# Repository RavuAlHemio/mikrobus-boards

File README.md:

# mikroBUS Boards

An assortment of boards that should be compatible with [MikroElektronika](https://www.mikroe.com/)'s [mikroBUS standard](https://download.mikroe.com/documents/standards/mikrobus/mikrobus-standard-specification-v200.pdf).

The designs are experimental. They are provided without warranty that the resulting boards will be fit for purpose and without warranty that they will not damage the connected devices.

## Boards

* `i2c-spi-jumper-mikrobus-board`: an I²C-to-SPI interface similar to the [_I2C to SPI Click_](https://www.mikroe.com/i2c-to-spi-click) (MIKROE-3743) and using the same chip ([NXP SC18IS602BIPW/S8HP](https://www.nxp.com/part/SC18IS602BIPW)), but with pin header jumpers instead of re-soldering 0Ω SMD "resistors" to set the I²C address. Perfect for people with no fine motor skills, like myself.

* `i2c-spi-jumper-mikrobus-board-var2`: another I²C-to-SPI interface with jumpers, but using the [NXP SC18IS606PW](https://www.nxp.com/part/SC18IS606PW), since the SC18IS602BIPW/S8HP is end-of-life. A different board is needed because the new chip has a different pinout.

* `i2c-spi-oled-mikrobus-board`: an I²C-to-SPI interface with a pinout that helps interoperability with the [_OLED C Click_] (https://www.mikroe.com/oled-c-click) (MIKROE-1585) by making some of its additional non-SPI pins accessible via I²C while isolating them from the microcontroller. To simplify the traces and keep the board a reasonable size, instead of providing a second pair of mikroBUS sockets to connect the SPI-enabled device, the design provides a [mikroBUS Shuttle](https://www.mikroe.com/mikrobus-shuttle) pin header.

* `i2c-uart-mikrobus-board`: just as the I²C-to-SPI boards allow SPI devices to be controlled via I²C, this board allows UART devices to be contacted via I²C. Based around the [NXP SC16IS740IPW](https://www.nxp.com/part/SC16IS740IPW). This board also provides a [mikroBUS Shuttle](https://www.mikroe.com/mikrobus-shuttle) pin header to connect the UART board. The I²C address is set using rotary switches.

* `knx-mikrobus-board`: a KNX bus coupling unit (BCU) that translates between KNX and UART. Based around the [onsemi NCN5130](https://www.onsemi.com/products/interfaces/wired-transceivers-modems/ncn5130) but should also work with the pin-compatible [onsemi NCN5121](https://www.onsemi.com/products/interfaces/wired-transceivers-modems/ncn5121).

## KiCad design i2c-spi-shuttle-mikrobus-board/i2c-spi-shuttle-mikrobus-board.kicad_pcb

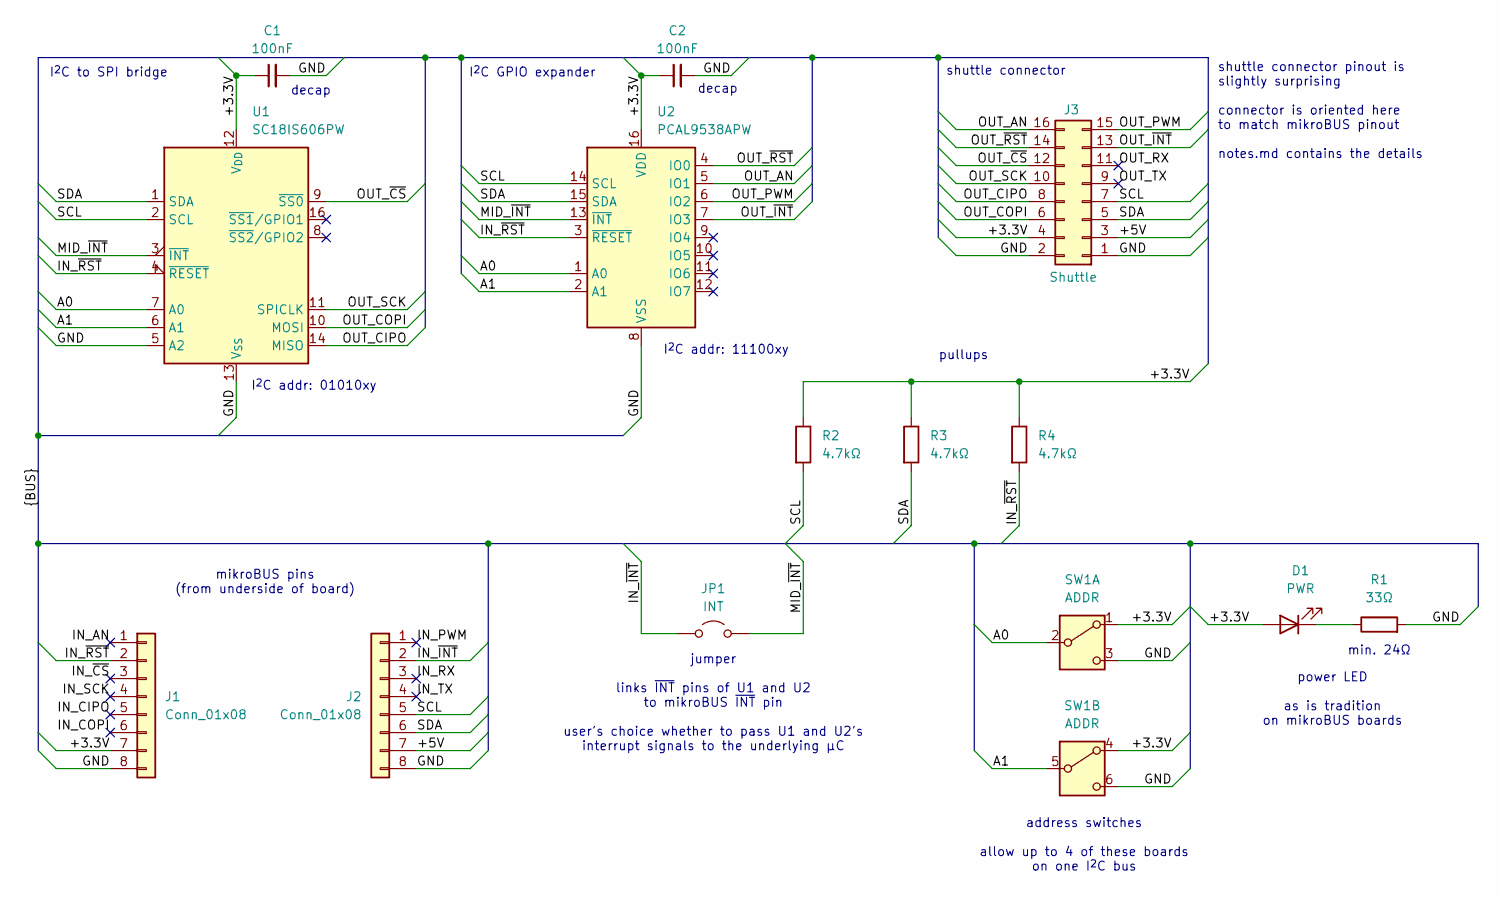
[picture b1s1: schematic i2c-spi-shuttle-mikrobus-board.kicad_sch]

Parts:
C1, C2: 100nF; C_0402_1005Metric; LCSC C307331
D1: PWR; LED_0805_2012Metric; LCSC C2297
J1, J2: Conn_01x08; PinHeader_1x08_P2.54mm_Vertical
J3: Shuttle; CNC_3221-16-0300-00; LCSC C5338669
JP1: INT; PinHeader_1x02_P2.54mm_Vertical
R1: 33Ω; R_0603_1608Metric; LCSC C23140
R2, R3, R4: 4.7kΩ; R_0402_1005Metric; LCSC C25900
SW1: ADDR; Nidec_Copal_CAS-D20A; LCSC C3664582
U1: SC18IS606PW; TSSOP-16_4.4x5mm_P0.65mm; LCSC C5190384
U2: PCAL9538APW; TSSOP-16_4.4x5mm_P0.65mm; LCSC C2652336

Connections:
/+3.3V: C1.1, C2.1, D1.2 (A), J1.7, J3.4, R2.1, R3.1, R4.1, SW1.1 (A), SW1.4 (A), U1.12 (V_{DD}), U1.15 (V_{DD}), U2.16 (VDD)
/+5V: J2.7, J3.3
/A0: SW1.2 (B), U1.7 (A0), U2.1 (A0)
/A1: SW1.5 (B), U1.6 (A1), U2.2 (A1)
/GND: C1.2, C2.2, J1.8, J2.8, J3.1, J3.2, R1.2, SW1.3 (C), SW1.6 (C), U1.5 (A2), U1.13 (V_{SS}), U2.8 (VSS)
/IN_AN: J1.1
/IN_CIPO: J1.5
/IN_COPI: J1.6
/IN_PWM: J2.1
/IN_RX: J2.3
/IN_SCK: J1.4
/IN_TX: J2.4
/IN_~CS: J1.3
/IN_~INT: J2.2, JP1.1 (A)
/IN_~RST: J1.2, R4.2, U1.4 (~RESET), U2.3 (~RESET)
/MID_~INT: JP1.2 (B), U1.3 (~INT), U2.13 (~INT)
/OUT_AN: J3.16, U2.5 (IO1)
/OUT_CIPO: J3.8, U1.14 (MISO)
/OUT_COPI: J3.6, U1.10 (MOSI)
/OUT_PWM: J3.15, U2.6 (IO2)
/OUT_RX: J3.11
/OUT_SCK: J3.10, U1.11 (SPICLK)
/OUT_TX: J3.9
/OUT_~CS: J3.12, U1.9 (~SS0)
/OUT_~INT: J3.13, U2.7 (IO3)
/OUT_~RST: J3.14, U2.4 (IO0)
/SCL: J2.5, J3.7, R2.2, U1.2 (SCL), U2.14 (SCL)
/SDA: J2.6, J3.5, R3.2, U1.1 (SDA), U2.15 (SDA)
unnamed: D1.1 (K), R1.1

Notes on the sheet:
address switches allow up to 4 of these boards on one I^{2}C bus
power LED as is tradition on mikroBUS boards
I^{2}C GPIO expander
min. 24Ω
I^{2}C to SPI bridge
shuttle connector pinout is slightly surprising connector is oriented here to match mikroBUS pinout notes.md contains the details
decap
jumper links ~{INT} pins of U1 and U2 to mikroBUS ~{INT} pin user's choice whether to pass U1 and U2's interrupt signals to the underlying µC
mikroBUS pins (from underside of board)
pullups
shuttle connector
I^{2}C addr: 11100xy
I^{2}C addr: 01010xy

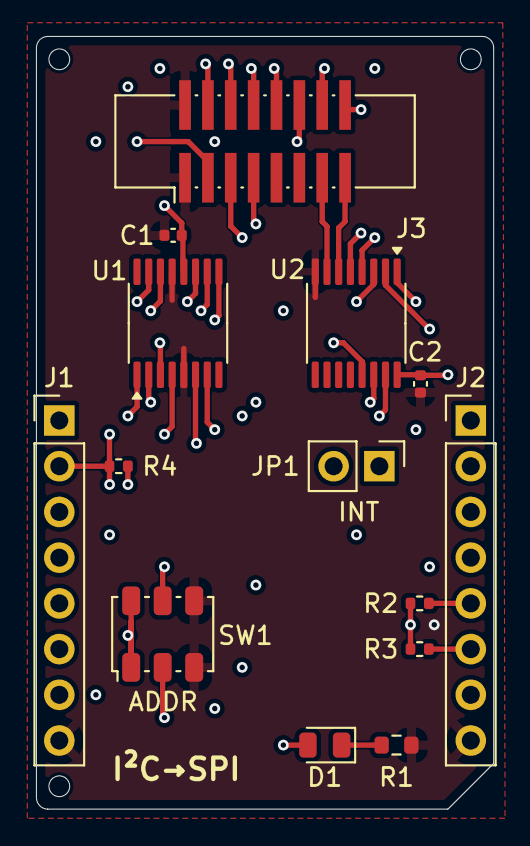
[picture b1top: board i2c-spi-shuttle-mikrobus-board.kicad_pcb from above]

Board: 4 copper layers, 25.4 x 42.9 mm, 14 parts (0 on the bottom side), 19 nets.

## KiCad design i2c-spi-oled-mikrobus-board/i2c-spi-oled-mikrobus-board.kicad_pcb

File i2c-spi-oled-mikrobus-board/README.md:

# `i2c-spi-oled-mikrobus-board`

I²C-to-SPI interface board with most mikroBUS pins controllable via I²C.

Combines two chips: SC18IS606PW (I²C-to-SPI) and PCA9557PW (I²C-to-GPIO).

## Addressing

Three bits of the address are chosen through the three jumpers on JP1. The bits are numbered, from
top to bottom, A0, A1, and A2. Bridging the left and middle pins with the jumper sets that bit to 0;
bridging the middle and right pins sets the bit to 1.

Once the jumpers are set, the following addresses are assigned to the chips:

| chip        | MSB | b5 | b4 | b3 | b2 | b1 | LSB | (R/W) |
| ----------- | --- | -- | -- | -- | -- | -- | --- | ----- |
| SC18IS606PW | 0   | 1  | 0  | 1  | A2 | A1 | A0  |       |
| PCA9557PW   | 0   | 0  | 1  | 1  | A2 | A1 | A0  |       |

### Communication

The shuttle board's peripheral select pin is connected to the SC18IS606PW's ¬SS0 pin. Therefore, to
send data via SPI, use function 0x01.

The non-SPI pins are connected to the PCA9557PW as follows:

| PCA9557PW | shuttle board |
| --------- | ------------- |
| P0        | ¬INT          |
| P1        | D/¬C          |
| P2        | EN            |
| P3        | R/¬W          |
| P4        | ¬RST          |

Pins P5 through P7 are unconnected.

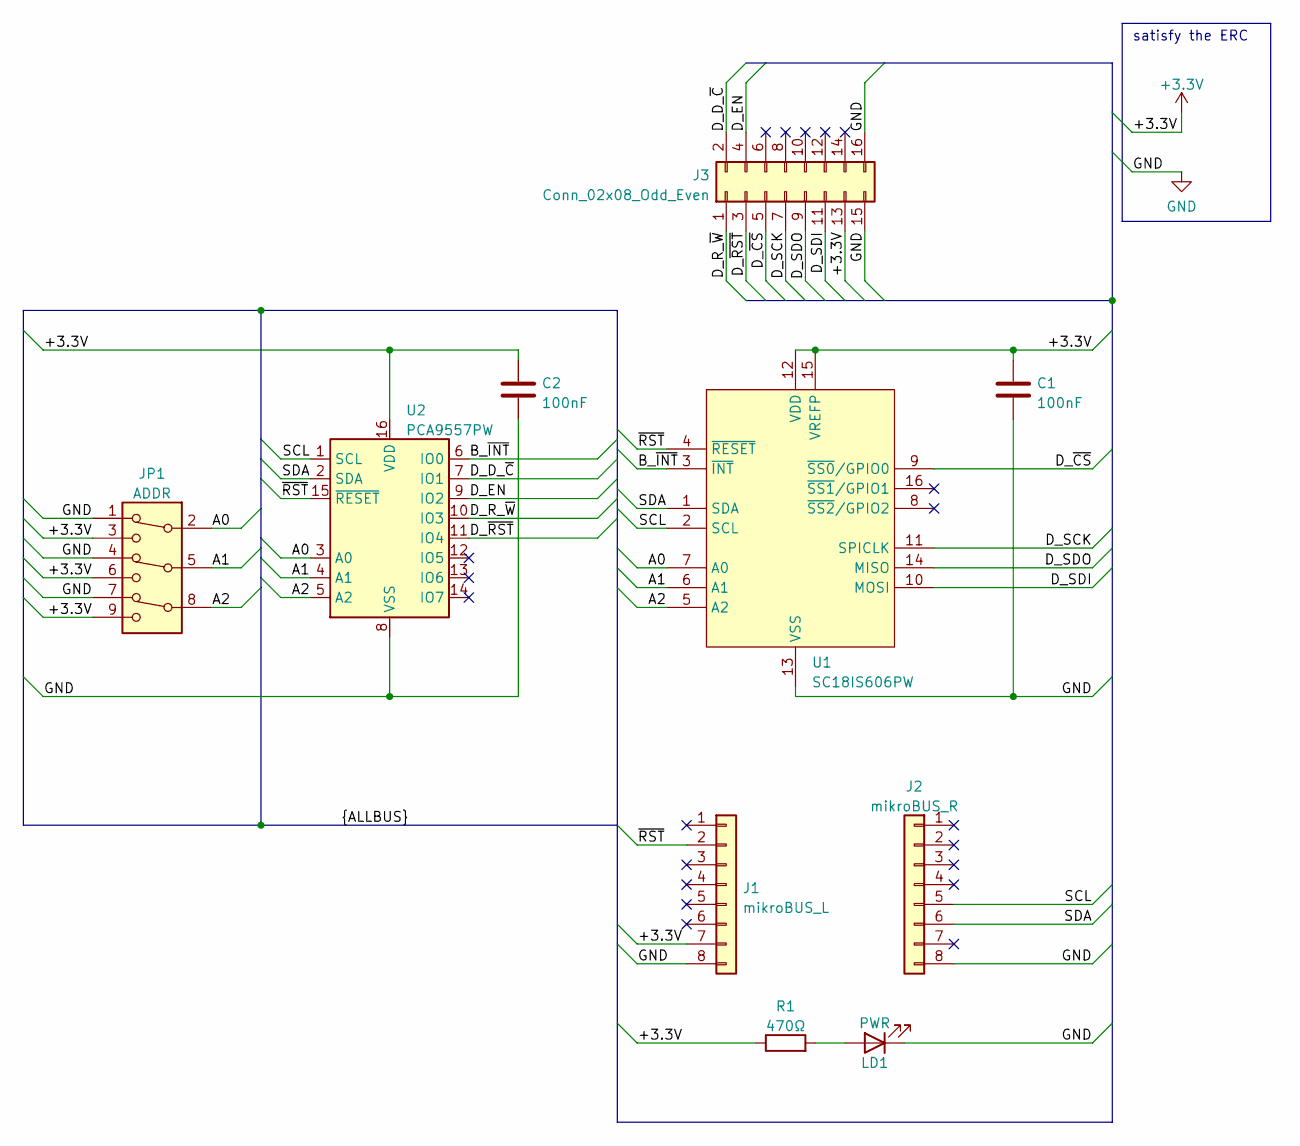
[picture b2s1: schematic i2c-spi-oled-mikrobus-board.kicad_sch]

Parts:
C1, C2: 100nF; C_0402_1005Metric; LCSC C307331
J1: mikroBUS_L; PinHeader_1x08_P2.54mm_Vertical
J2: mikroBUS_R; PinHeader_1x08_P2.54mm_Vertical
J3: Conn_02x08_Odd_Even; CNC_3221-16-0300-00; LCSC C5338669
JP1: ADDR; PinHeader_3x03_P2.54mm_Vertical
LD1: PWR; LED_0603_1608Metric; LCSC C72043
R1: 470Ω; R_0603_1608Metric; LCSC C23179
U1: SC18IS606PW; TSSOP-16_4.4x5mm_P0.65mm; LCSC C5190384
U2: PCA9557PW; TSSOP-16_4.4x5mm_P0.65mm; LCSC C141380

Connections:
+3.3V: C1.2, C2.2, J1.7, J3.13, JP1.3, JP1.6, JP1.9, R1.1, U1.12 (VDD), U1.15 (VREFP), U2.16 (VDD)
/A0: JP1.2, U1.7 (A0), U2.3 (A0)
/A1: JP1.5, U1.6 (A1), U2.4 (A1)
/A2: JP1.8, U1.5 (A2), U2.5 (A2)
/B_~INT: U1.3 (~INT), U2.6 (IO0)
/D_D_~C: J3.2, U2.7 (IO1)
/D_EN: J3.4, U2.9 (IO2)
/D_R_~W: J3.1, U2.10 (IO3)
/D_SCK: J3.7, U1.11 (SPICLK)
/D_SDI: J3.11, U1.10 (MOSI)
/D_SDO: J3.9, U1.14 (MISO)
/D_~CS: J3.5, U1.9 (~SS0/GPIO0)
/D_~RST: J3.3, U2.11 (IO4)
/SCL: J2.5, U1.2 (SCL), U2.1 (SCL)
/SDA: J2.6, U1.1 (SDA), U2.2 (SDA)
/~RST: J1.2, U1.4 (~RESET), U2.15 (~RESET)
GND: C1.1, C2.1, J1.8, J2.8, J3.15, J3.16, JP1.1, JP1.4, JP1.7, LD1.1 (K), U1.13 (VSS), U2.8 (VSS)
unnamed: LD1.2 (A), R1.2

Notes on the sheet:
satisfy the ERC

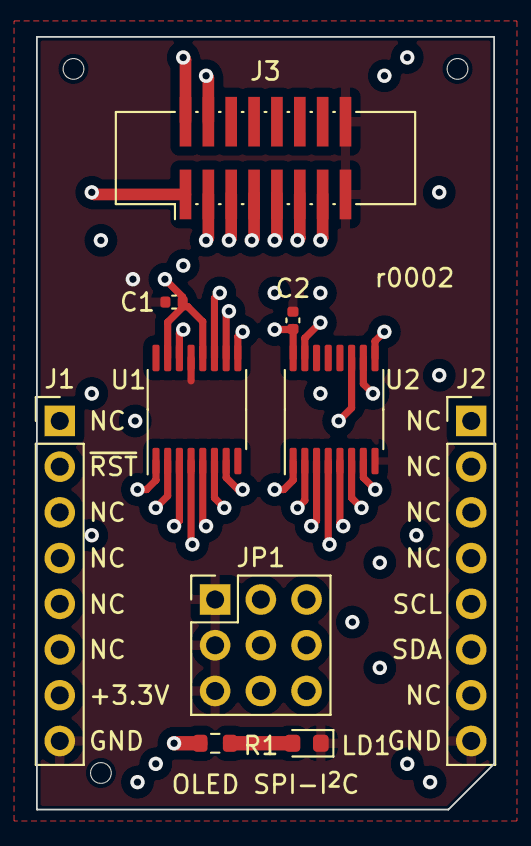
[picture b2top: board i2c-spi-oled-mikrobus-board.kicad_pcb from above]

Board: 4 copper layers, 25.4 x 42.9 mm, 10 parts (0 on the bottom side), 18 nets.

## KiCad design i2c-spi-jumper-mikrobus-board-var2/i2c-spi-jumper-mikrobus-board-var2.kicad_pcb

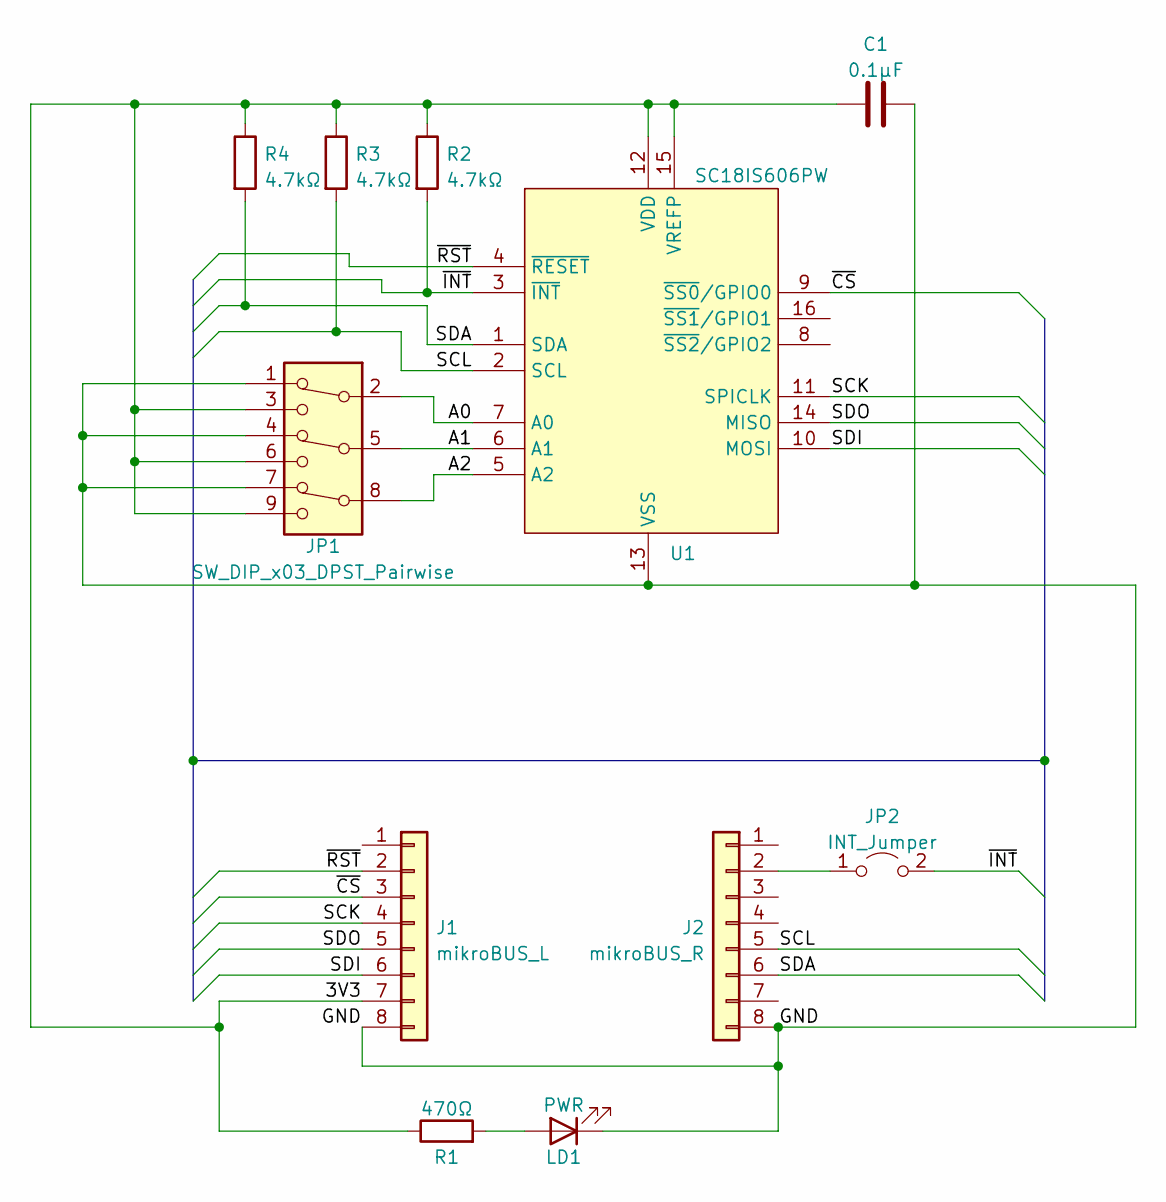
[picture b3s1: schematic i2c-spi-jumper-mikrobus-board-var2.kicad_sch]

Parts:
C1: 0.1µF; C_0402_1005Metric; LCSC C307331
J1: mikroBUS_L; PinHeader_1x08_P2.54mm_Vertical
J2: mikroBUS_R; PinHeader_1x08_P2.54mm_Vertical
JP1: SW_DIP_x03_DPST_Pairwise; PinHeader_3x03_P2.54mm_Vertical
JP2: INT_Jumper; PinHeader_1x02_P2.54mm_Vertical
LD1: PWR; LED_0603_1608Metric; LCSC C72043
R1: 470Ω; R_0603_1608Metric; LCSC C23179
R2, R3, R4: 4.7kΩ; R_0402_1005Metric; LCSC C25900
U1: SC18IS606PW; TSSOP-16_4.4x5mm_P0.65mm; LCSC C5190384

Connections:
/3V3: C1.1, J1.7, JP1.3, JP1.6, JP1.9, R1.1, R2.1, R3.1, R4.1, U1.12 (VDD), U1.15 (VREFP)
/A0: JP1.2, U1.7 (A0)
/A1: JP1.5, U1.6 (A1)
/A2: JP1.8, U1.5 (A2)
/GND: C1.2, J1.8, J2.8, JP1.1, JP1.4, JP1.7, LD1.1 (K), U1.13 (VSS)
/SCK: J1.4, U1.11 (SPICLK)
/SCL: J2.5, R3.2, U1.2 (SCL)
/SDA: J2.6, R4.2, U1.1 (SDA)
/SDI: J1.6, U1.10 (MOSI)
/SDO: J1.5, U1.14 (MISO)
/~CS: J1.3, U1.9 (~SS0/GPIO0)
/~INT: JP2.2 (B), R2.2, U1.3 (~INT)
/~RST: J1.2, U1.4 (~RESET)
unnamed: J2.2, JP2.1 (A)
unnamed: LD1.2 (A), R1.2

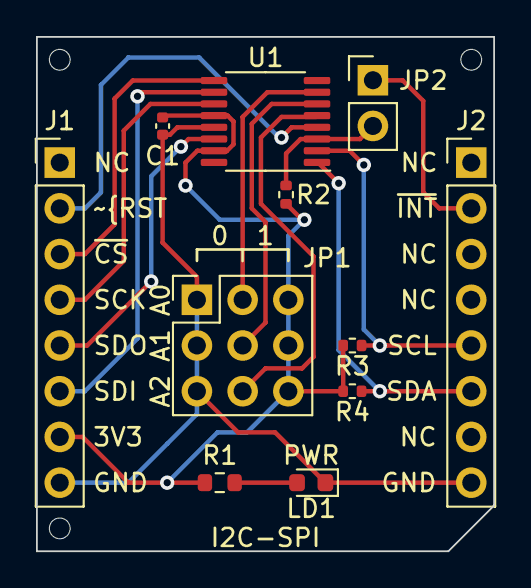
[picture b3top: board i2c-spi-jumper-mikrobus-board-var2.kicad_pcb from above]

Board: 2 copper layers, 25.4 x 28.6 mm, 11 parts (0 on the bottom side), 15 nets.

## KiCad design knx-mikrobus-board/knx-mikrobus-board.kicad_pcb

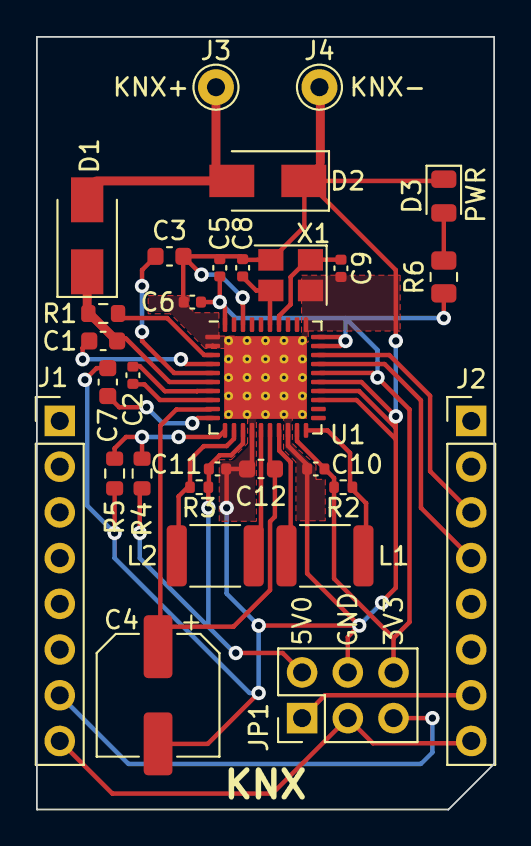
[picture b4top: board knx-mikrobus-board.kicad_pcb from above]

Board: 2 copper layers, 25.4 x 42.9 mm, 30 parts (0 on the bottom side), 25 nets.

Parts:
C1: 47nF; C_0603_1608Metric
C2: 220nF; C_0402_1005Metric
C3, C12: 100nF; C_0603_1608Metric
C4: 100μF; CP_Elec_6.3x5.7
C5, C6: 100nF; C_0402_1005Metric
C7: 1µF; C_0603_1608Metric
C8, C9: 9pF; C_0402_1005Metric
C10, C11: 10µF; C_0402_1005Metric
D1: SS16; D_SMA
D2: SMAJ40CA; D_SMA
D3: LED; LED_0805_2012Metric
J1: mikroBUS_L; PinHeader_1x08_P2.54mm_Vertical
J2: mikroBUS_R; PinHeader_1x08_P2.54mm_Vertical
J3: KNX+; Pin_D1.0mm_L10.0mm
J4: KNX-; Pin_D1.0mm_L10.0mm
JP1: SW_DIP_x03; PinHeader_2x03_P2.54mm_Vertical
L1, L2: 220µH; L_1812_4532Metric
R1: 27Ω; R_0603_1608Metric
R2, R3: 1Ω; R_0402_1005Metric
R4: 180kΩ; R_0603_1608Metric
R5: 56kΩ; R_0603_1608Metric
R6: 470Ω; R_0805_2012Metric
U1: NCN5130; QFN-40-1EP_6x6mm_P0.5mm_EP4.6x4.6mm_ThermalVias
X1: 16MHz; Crystal_SMD_3225-4Pin_3.2x2.5mm

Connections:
/+3.3V: J1.7, JP1.5
/+5V: J2.7, JP1.1
/GND: J1.8, J2.8, JP1.3
/RX: J2.4, U1.27 (SDI/RXD)
/TX: J2.3, U1.28 (SDO/TXD)
/knx-logic/+3.3V: C5.2, C6.2, C10.1, JP1.6, R2.1, R6.1, U1.19 (VDD1), U1.26 (CSB/UC1), U1.29 (SCK/UC2), U1.30 (VDDD), U1.40 (VDDA)
/knx-logic/+5V: C11.1, JP1.2, R3.1, R4.1, U1.13 (VDD2)
/knx-logic/GND: C3.2, C4.2, C5.1, C6.1, C7.2, C8.2, C9.2, C10.2, C11.2, C12.1, D2.1 (A1), D3.1 (K), J4.1, JP1.4, R5.2, U1.1 (VSSA), U1.2 (VBUS2), U1.14 (VSS2), U1.18 (VSS1), U1.23 (MODE1), U1.24 (MODE2), U1.25 (TREQ), U1.31 (VSSD), U1.38 (FANIN), U1.41 (GND_PLANE), X1.2, X1.4
/knx-logic/KNX_+: D1.2 (A), D2.2 (A2), J3.1
unnamed: C1.1, U1.4 (CCP)
unnamed: C1.2, D1.1 (K), R1.2, U1.6 (VBUS1)
unnamed: C2.1, U1.8 (CEQ2)
unnamed: C2.2, U1.7 (CEQ1)
unnamed: C3.1, U1.5 (CAV)
unnamed: C7.1, U1.10 (V20V)
unnamed: C8.1, U1.35 (XTAL1), X1.3
unnamed: C9.1, U1.34 (XTAL2), X1.1
unnamed: C4.1, C12.2, U1.9 (VFILT), U1.16 (VIN)
unnamed: D3.2 (A), R6.2
unnamed: L1.1, R2.2, U1.20 (VDD1M)
unnamed: L1.2, U1.17 (VSW1)
unnamed: L2.1, R3.2, U1.12 (VDD2MC)
unnamed: L2.2, U1.15 (VSW2)
unnamed: R1.1, U1.3 (TXO)
unnamed: R4.2, R5.1, U1.11 (VDD2MV)

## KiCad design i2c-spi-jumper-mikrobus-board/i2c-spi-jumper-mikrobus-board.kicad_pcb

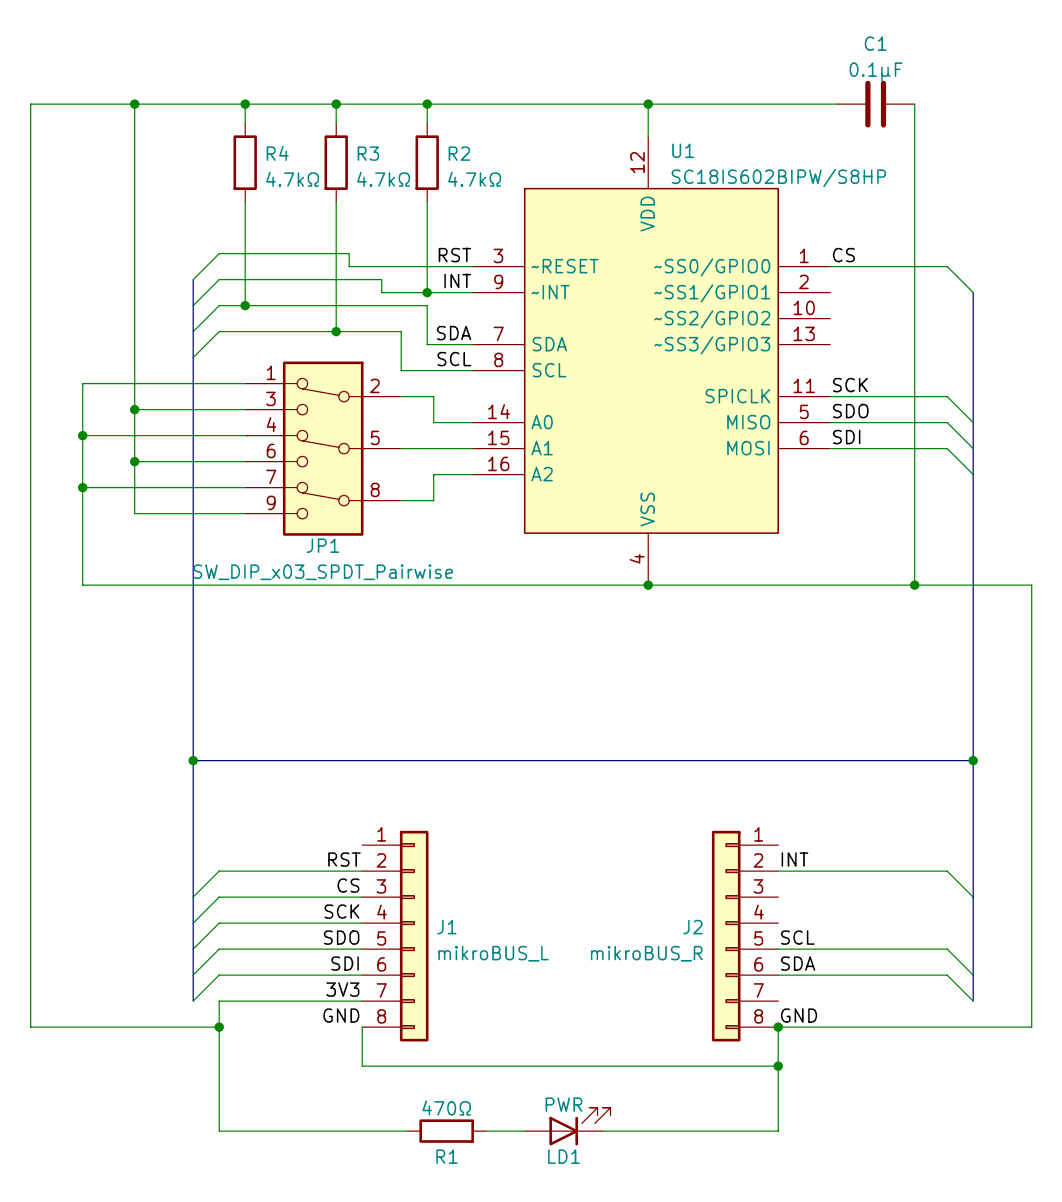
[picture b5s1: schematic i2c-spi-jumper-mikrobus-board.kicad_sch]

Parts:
C1: 0.1µF; C_0402_1005Metric; LCSC C307331
J1: mikroBUS_L; PinHeader_1x08_P2.54mm_Vertical
J2: mikroBUS_R; PinHeader_1x08_P2.54mm_Vertical
JP1: SW_DIP_x03_SPDT_Pairwise; PinHeader_3x03_P2.54mm_Vertical
LD1: PWR; LED_0805_2012Metric; LCSC C73548
R1: 470Ω; R_0805_2012Metric; LCSC C17673
R2, R3, R4: 4.7kΩ; R_0402_1005Metric; LCSC C25900
U1: SC18IS602BIPW/S8HP; TSSOP-16_4.4x5mm_P0.65mm; LCSC C2678036

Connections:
/3V3: C1.1, J1.7, JP1.3, JP1.6, JP1.9, R1.1, R2.1, R3.1, R4.1, U1.12 (VDD)
/CS: J1.3, U1.1 (~SS0/GPIO0)
/GND: C1.2, J1.8, J2.8, JP1.1, JP1.4, JP1.7, LD1.1 (K), U1.4 (VSS)
/INT: J2.2, R2.2, U1.9 (~INT)
/RST: J1.2, U1.3 (~RESET)
/SCK: J1.4, U1.11 (SPICLK)
/SCL: J2.5, R3.2, U1.8 (SCL)
/SDA: J2.6, R4.2, U1.7 (SDA)
/SDI: J1.6, U1.6 (MOSI)
/SDO: J1.5, U1.5 (MISO)
unnamed: JP1.2, U1.14 (A0)
unnamed: JP1.5, U1.15 (A1)
unnamed: JP1.8, U1.16 (A2)
unnamed: LD1.2 (A), R1.2

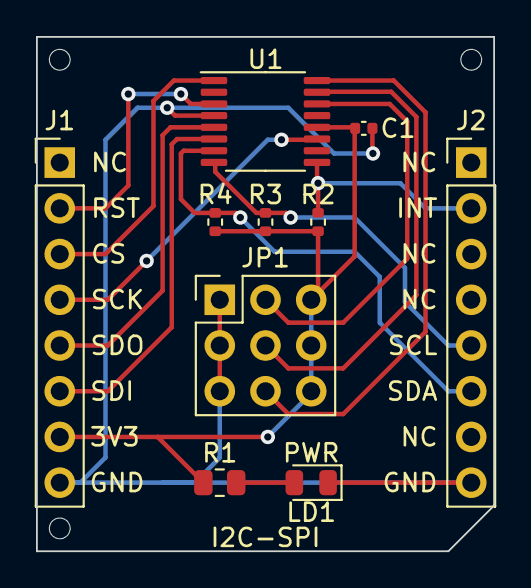
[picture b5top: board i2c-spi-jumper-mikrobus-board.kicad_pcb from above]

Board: 2 copper layers, 25.4 x 28.6 mm, 10 parts (0 on the bottom side), 14 nets.

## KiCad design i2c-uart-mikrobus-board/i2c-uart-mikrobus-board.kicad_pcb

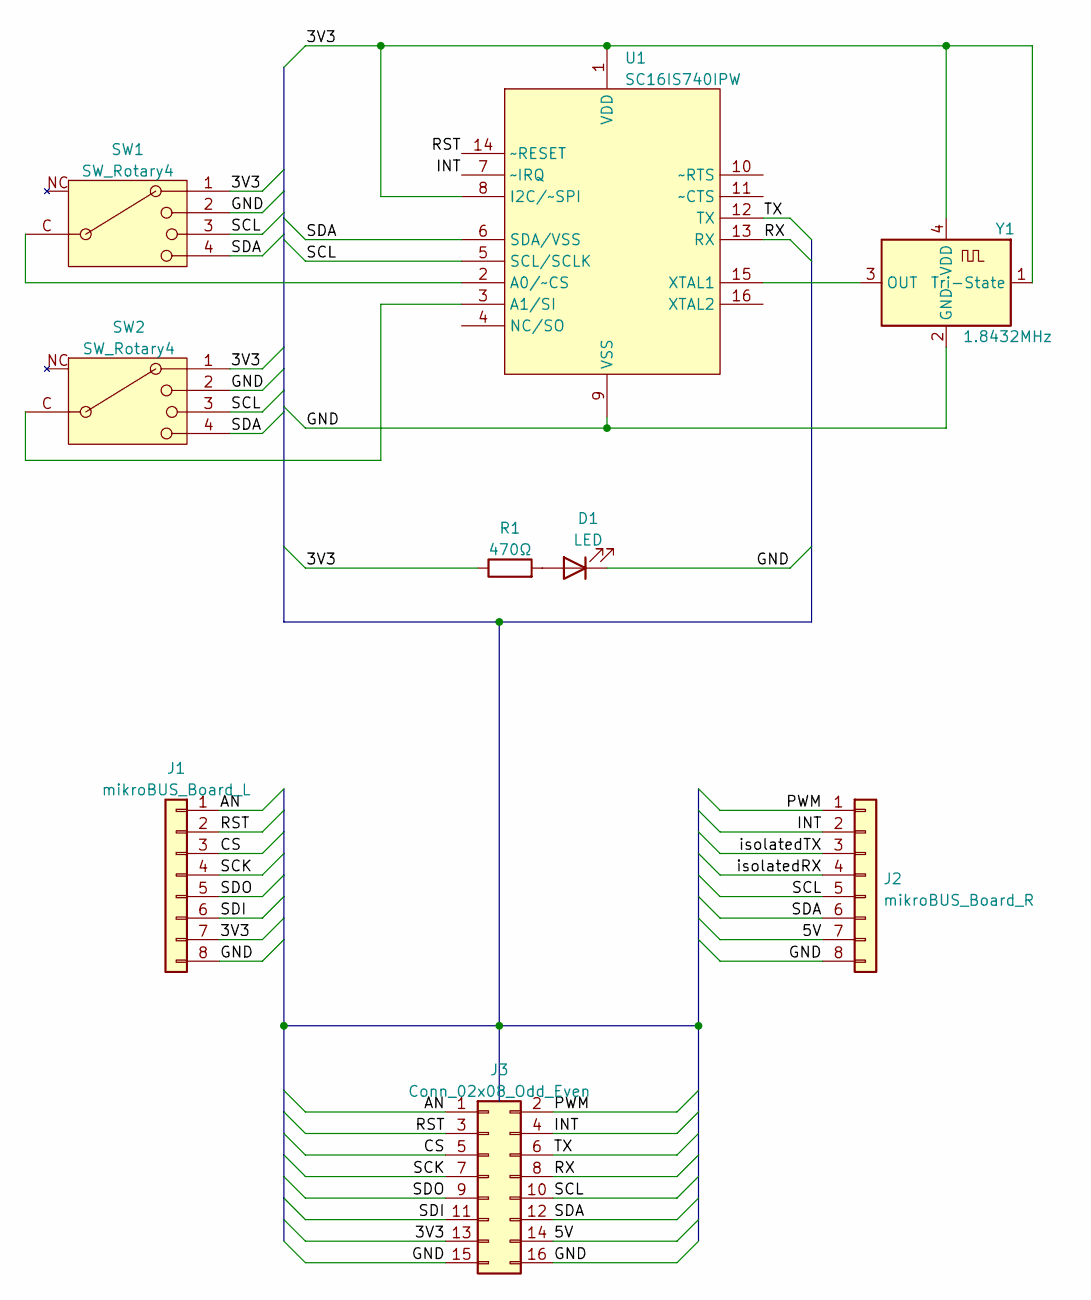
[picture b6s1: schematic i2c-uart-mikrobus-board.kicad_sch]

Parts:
D1: LED; LED_0805_2012Metric
J1: mikroBUS_Board_L; PinHeader_1x08_P2.54mm_Vertical
J2: mikroBUS_Board_R; PinHeader_1x08_P2.54mm_Vertical
J3: Conn_02x08_Odd_Even; CNC_3221-16-0300-00
R1: 470Ω; R_0805_2012Metric
SW1, SW2: SW_Rotary4; Nidec_Copal_CS-4-14NB; Mouser 229-CS-4-14NTB
U1: SC16IS740IPW; TSSOP-16_4.4x5mm_P0.65mm; Mouser 771-SC16IS0IPW128
Y1: 1.8432MHz; Oscillator_SMD_ECS_2520MV-xxx-xx-4Pin_2.5x2.0mm; Mouser 520-3225MVLC-018CNTR

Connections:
/3V3: J1.7, J3.13, R1.1, SW1.1, SW2.1, U1.1 (VDD), U1.8 (I2C/~SPI), Y1.1 (Tri-State), Y1.4 (VDD)
/5V: J2.7, J3.14
/AN: J1.1, J3.1
/CS: J1.3, J3.5
/GND: D1.1 (K), J1.8, J2.8, J3.15, J3.16, SW1.2, SW2.2, U1.9 (VSS), Y1.2 (GND)
/INT: J2.2, J3.4, U1.7 (~IRQ)
/PWM: J2.1, J3.2
/RST: J1.2, J3.3, U1.14 (~RESET)
/RX: J3.8, U1.13 (RX)
/SCK: J1.4, J3.7
/SCL: J2.5, J3.10, SW1.3, SW2.3, U1.5 (SCL/SCLK)
/SDA: J2.6, J3.12, SW1.4, SW2.4, U1.6 (SDA/VSS)
/SDI: J1.6, J3.11
/SDO: J1.5, J3.9
/TX: J3.6, U1.12 (TX)
/isolatedRX: J2.4
/isolatedTX: J2.3
unnamed: D1.2 (A), R1.2
unnamed: SW1.C, U1.2 (A0/~CS)
unnamed: SW2.C, U1.3 (A1/SI)
unnamed: U1.15 (XTAL1), Y1.3 (OUT)

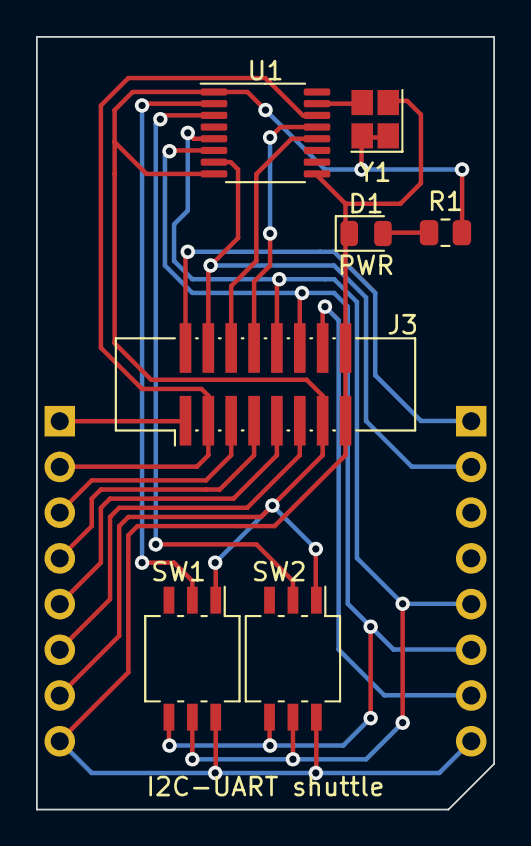
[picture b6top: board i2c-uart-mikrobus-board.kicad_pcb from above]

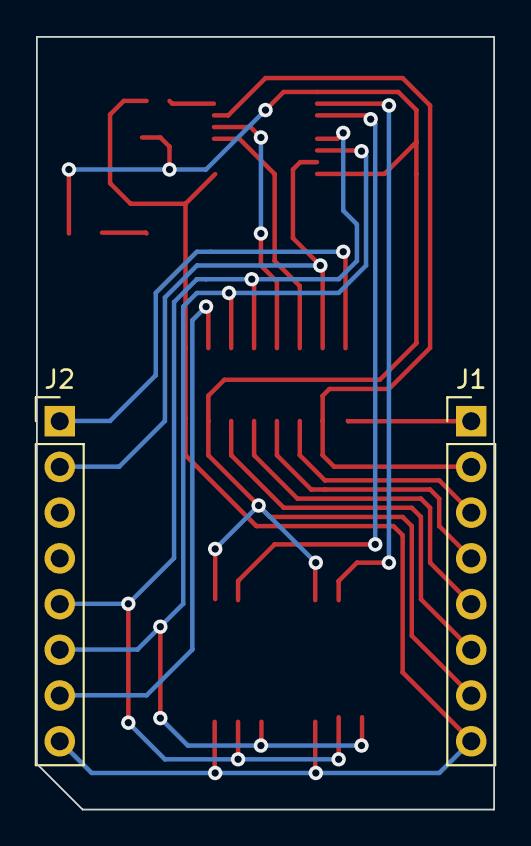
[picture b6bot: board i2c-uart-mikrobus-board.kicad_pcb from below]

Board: 2 copper layers, 25.4 x 42.9 mm, 9 parts (2 on the bottom side), 19 nets.

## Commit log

2022-10-17 i2c-uart: fix rotary switch orientation
2022-10-17 i2c-spi-jumper-var2: exclude THT headers from BOM
2022-10-17 i2c-spi-jumper-var2: fix LCSC number of chip
    we had the old one listed
2022-10-17 i2c-uart: center Shuttle pin header footprint
2022-10-17 i2c-spi-jumper: mounting holes are of type "Other"
2022-10-25 knx: add ground plane
2022-10-25 ignore jlcpcb subdirectory (outputs of JLCPCB Tools plugin)
2022-10-26 i2c-spi-jumper-var2: add JLCPCB mounting holes
2022-11-05 i2c-spi-jumper-var2: fix signal negation
2022-11-05 i2c-spi-jumper-var2: add jumper to enable/disable ~INT pin connection
    This allows mikroBUS boards like the OLED C click to be used with this
    board without causing their Enable pin, which shares its location with the
    ~Interrupt pin, to be pulled low after SPI communication completes.
2022-12-16 add I2C SPI OLED mikroBUS board
2022-12-16 make I2C interface symbol fit default grid
2022-12-16 i2c-spi-oled: also connect the R/~W pin
    the display doesn't need it (it will be held to GND) but we might reuse
    this board for other SPI components
2023-04-30 oled: add JLCPCB mounting holes
2023-04-30 oled: add README with pertinent I2C info
2023-07-23 README: fix description of i2c-spi-oled-mikrobus-board
2023-07-23 i2c-spi-oled: put ~RST signal on port expander too
2023-07-23 i2c-spi-oled: document P4
2025-07-05 notes: add note about ARM debug connector
2025-07-27 start i2c-spi-shuttle-mikrobus-board
    no progress yet because I'll be contributing symbols to KiCad first
2025-07-28 first version of i2c-spi-shuttle-mikrobus-board
    TODO:
    * purpose of board on silkscreen
    * some pin explanations on silkscreen (probably rear)
    * check if shuttle connector is oriented correctly!
    (MikroE schematics are inconsistent, test with multimeter)
2025-07-28 document more about the Shuttle boards
2025-07-28 fix shuttle pinout in schematic, clear PCB of tracks (we must reroute)
2025-07-29 ignore lock files
2025-07-29 route the I2C-SPI Shuttle board now that the pinout is fixed
2025-07-29 annotate schematic & board, pass +5V, update constraints
2025-07-29 add LCSC numbers
2025-07-30 notes: clarify Shuttle base connector orientation
2025-08-21 i2c spi shuttle: add mounting holes, JLC number placeholder, front label
